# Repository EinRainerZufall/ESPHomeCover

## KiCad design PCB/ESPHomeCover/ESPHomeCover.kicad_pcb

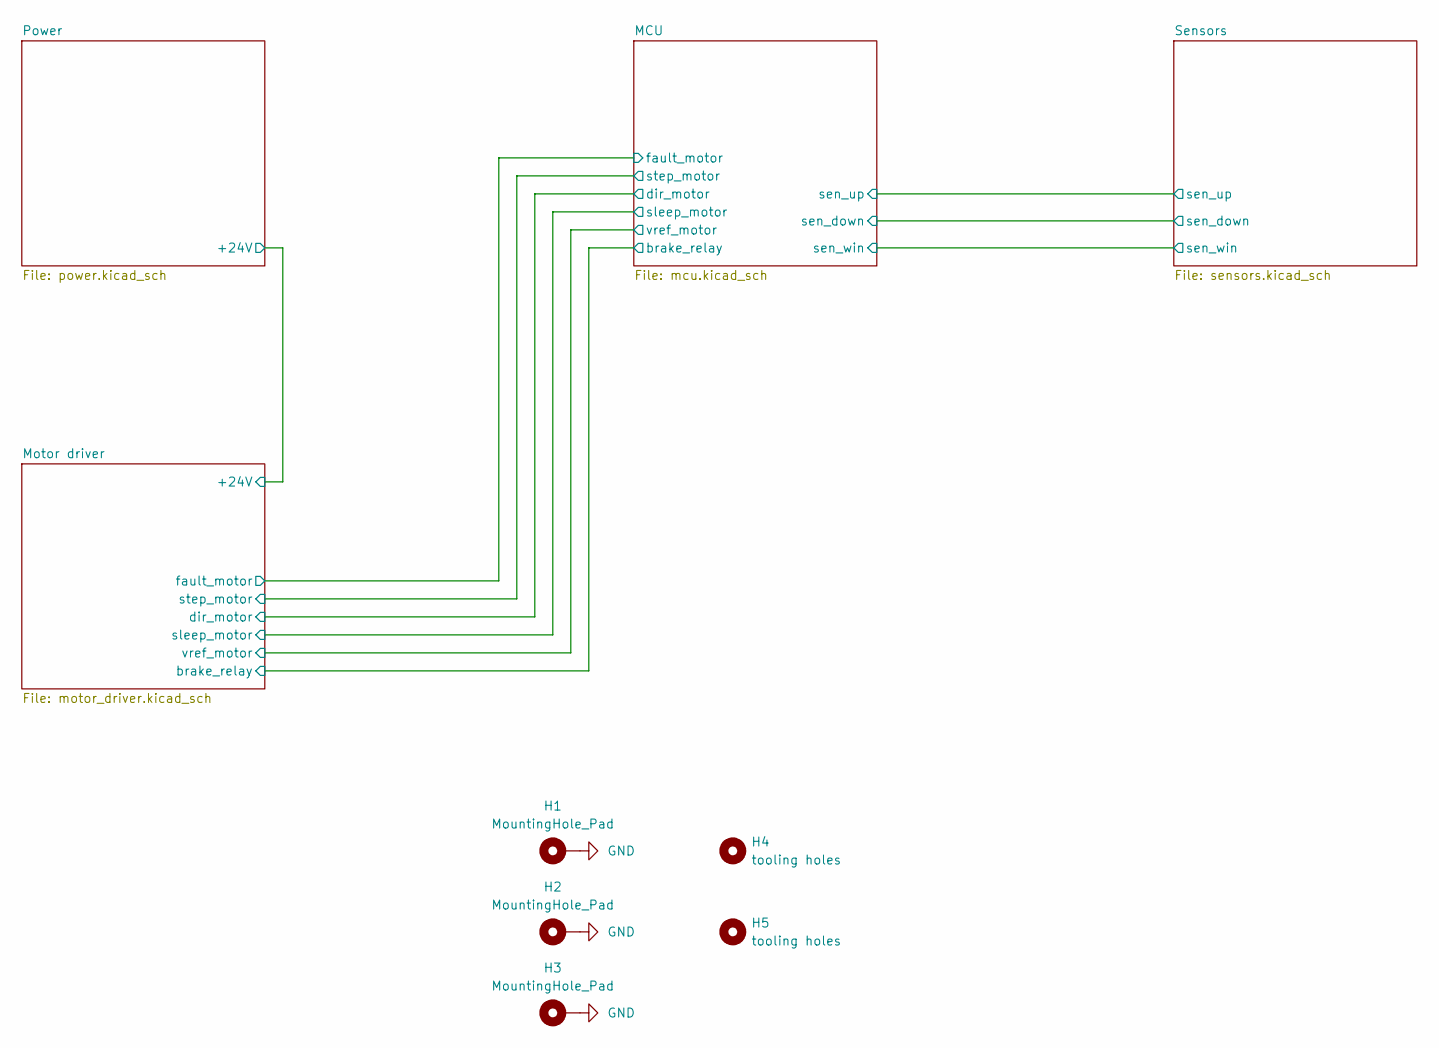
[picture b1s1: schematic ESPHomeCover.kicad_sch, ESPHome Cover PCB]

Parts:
H1, H2, H3: MountingHole_Pad; MountingHole_3.2mm_M3_ISO14580_Pad
H4, H5: tooling holes

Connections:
GND: H1.1, H2.1, H3.1; also elsewhere on the board

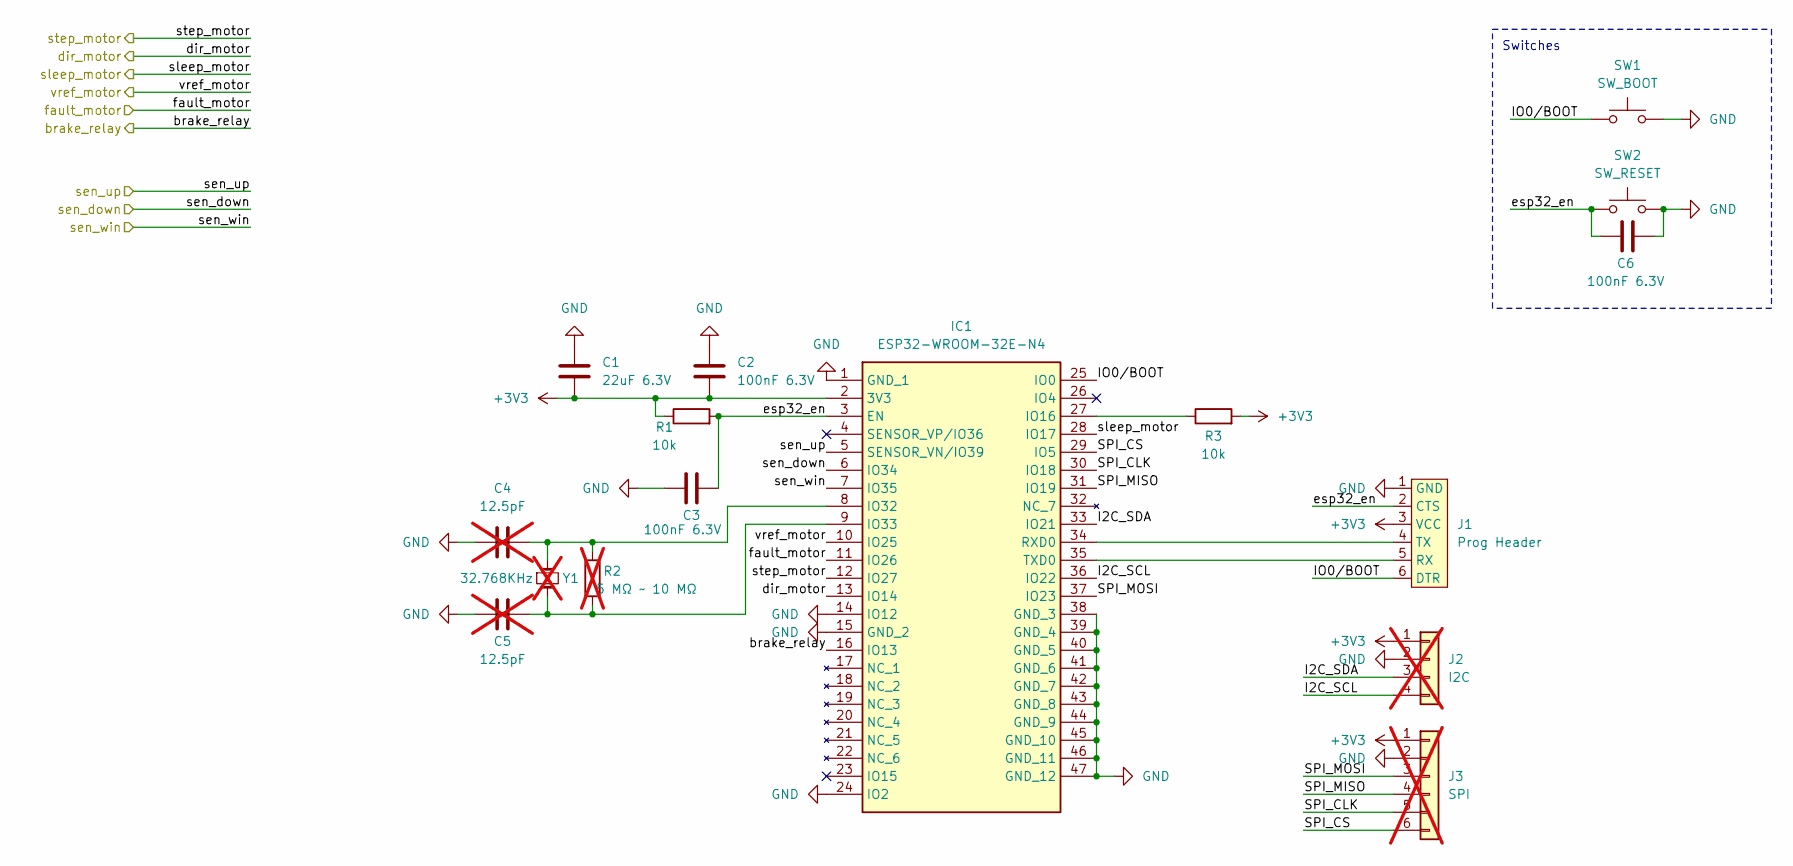
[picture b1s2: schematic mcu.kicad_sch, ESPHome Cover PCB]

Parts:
C1: 22uF 6.3V; C_0603_1608Metric; Mouser Part Number 963-MSASJ168BB5226MT; LCSC C159801
C2, C3, C6: 100nF 6.3V; C_0603_1608Metric; Mouser Part Number 581-06036C104JAT2A
C4, C5: 12.5pF; C_0603_1608Metric; not fitted
IC1: ESP32-WROOM-32E-N4; ESP32WROOM32EN4; Mouser Part Number 356-ESP32WRM32E132PH
J1: Prog Header
J2: I2C; JST_XH_B4B-XH-A_1x04_P2.50mm_Vertical; not fitted
J3: SPI; JST_XH_B6B-XH-A_1x06_P2.50mm_Vertical; not fitted
R1, R3: 10k; R_0805_2012Metric; Mouser Part Number 667-ERA-6AEB103V; LCSC C17414
R2: 5 MΩ ~ 10 MΩ; R_0805_2012Metric; not fitted
SW1: SW_BOOT; TL3302AF130QG; Mouser Part Number 612-TL3302AF130QG
SW2: SW_RESET; TL3302AF130QG; Mouser Part Number 612-TL3302AF130QG
Y1: 32.768KHz; Crystal_SMD_2012-2Pin_2.0x1.2mm; LCSC C5366544; not fitted

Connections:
+3V3: C1.2, C2.2, IC1.2 (3V3), J1.3 (VCC), J2.1, J3.1, R1.1, R3.2; also elsewhere on the board
/MCU/I2C_SCL: IC1.36 (IO22), J2.4
/MCU/I2C_SDA: IC1.33 (IO21), J2.3
/MCU/IO0/BOOT: IC1.25 (IO0), J1.6 (DTR), SW1.1
/MCU/SPI_CLK: IC1.30 (IO18), J3.5
/MCU/SPI_CS: IC1.29 (IO5), J3.6
/MCU/SPI_MISO: IC1.31 (IO19), J3.4
/MCU/SPI_MOSI: IC1.37 (IO23), J3.3
/MCU/brake_relay: IC1.16 (IO13); also elsewhere on the board
/MCU/dir_motor: IC1.13 (IO14); also elsewhere on the board
/MCU/esp32_en: C3.2, C6.2, IC1.3 (EN), J1.2 (CTS), R1.2, SW2.2
/MCU/fault_motor: IC1.11 (IO26); also elsewhere on the board
/MCU/sen_down: IC1.6 (IO34); also elsewhere on the board
/MCU/sen_up: IC1.5 (SENSOR_VN/IO39); also elsewhere on the board
/MCU/sen_win: IC1.7 (IO35); also elsewhere on the board
/MCU/sleep_motor: IC1.28 (IO17); also elsewhere on the board
/MCU/step_motor: IC1.12 (IO27); also elsewhere on the board
/MCU/vref_motor: IC1.10 (IO25); also elsewhere on the board
GND: C1.1, C2.1, C3.1, C4.1, C5.1, C6.1, IC1.1 (GND_1), IC1.14 (IO12), IC1.15 (GND_2), IC1.24 (IO2), IC1.38 (GND_3), IC1.39 (GND_4), IC1.40 (GND_5), IC1.41 (GND_6), IC1.42 (GND_7), IC1.43 (GND_8), IC1.44 (GND_9), IC1.45 (GND_10), IC1.46 (GND_11), IC1.47 (GND_12), J1.1 (GND), J2.2, J3.2, SW1.2, SW2.1; also elsewhere on the board
unnamed: IC1.27 (IO16), R3.1
unnamed: C4.2, IC1.8 (IO32), R2.2, Y1.1
unnamed: C5.2, IC1.9 (IO33), R2.1, Y1.2
unnamed: IC1.34 (RXD0), J1.4 (TX)
unnamed: IC1.35 (TXD0), J1.5 (RX)

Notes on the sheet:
Switches

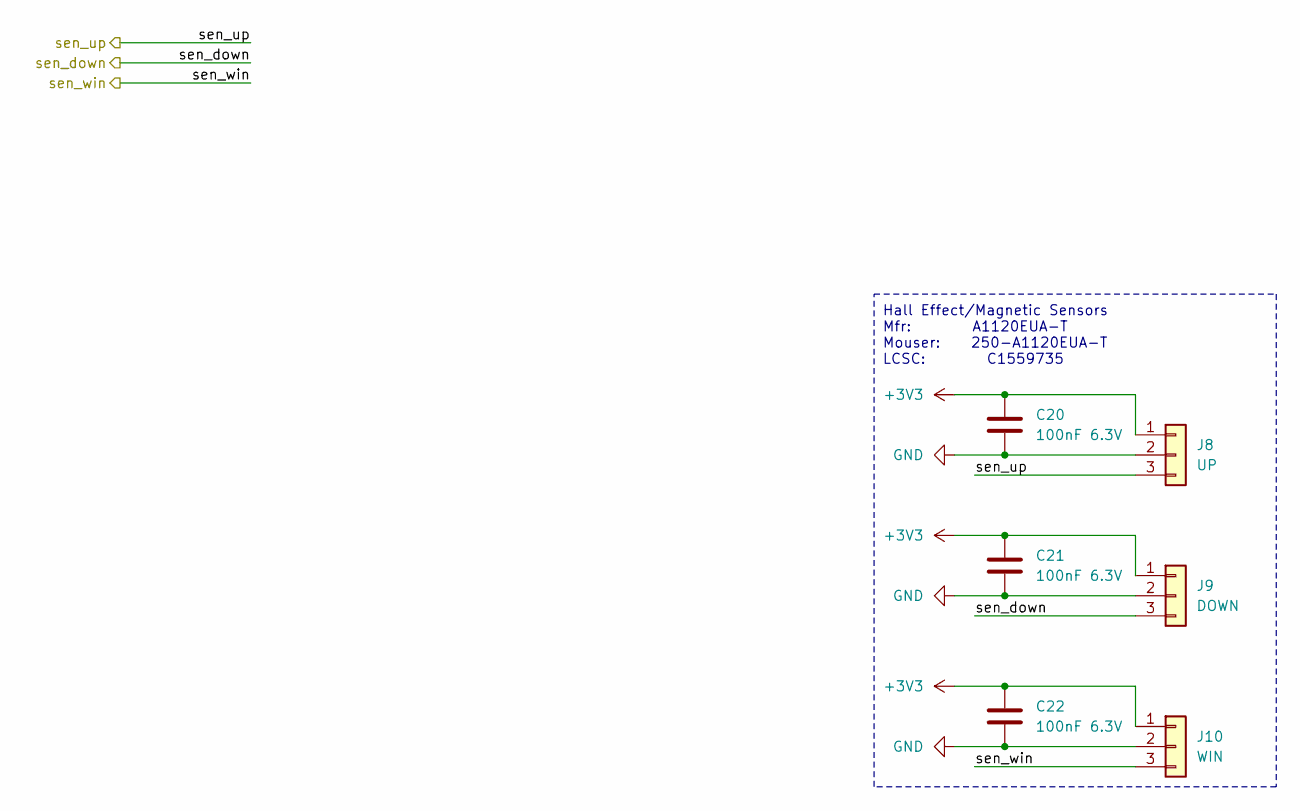
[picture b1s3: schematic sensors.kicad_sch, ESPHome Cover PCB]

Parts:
C20, C21, C22: 100nF 6.3V; C_0603_1608Metric; Mouser Part Number 581-06036C104JAT2A
J8: UP; JST_XH_B3B-XH-A_1x03_P2.50mm_Vertical
J9: DOWN; JST_XH_B3B-XH-A_1x03_P2.50mm_Vertical
J10: WIN; JST_XH_B3B-XH-A_1x03_P2.50mm_Vertical

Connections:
+3V3: C20.1, C21.1, C22.1, J8.1, J9.1, J10.1; also elsewhere on the board
/MCU/sen_down: J9.3; also elsewhere on the board
/MCU/sen_up: J8.3; also elsewhere on the board
/MCU/sen_win: J10.3; also elsewhere on the board
GND: C20.2, C21.2, C22.2, J8.2, J9.2, J10.2; also elsewhere on the board

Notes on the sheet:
Hall Effect/Magnetic Sensors Mfr: A1120EUA-T Mouser: 250-A1120EUA-T LCSC: C1559735

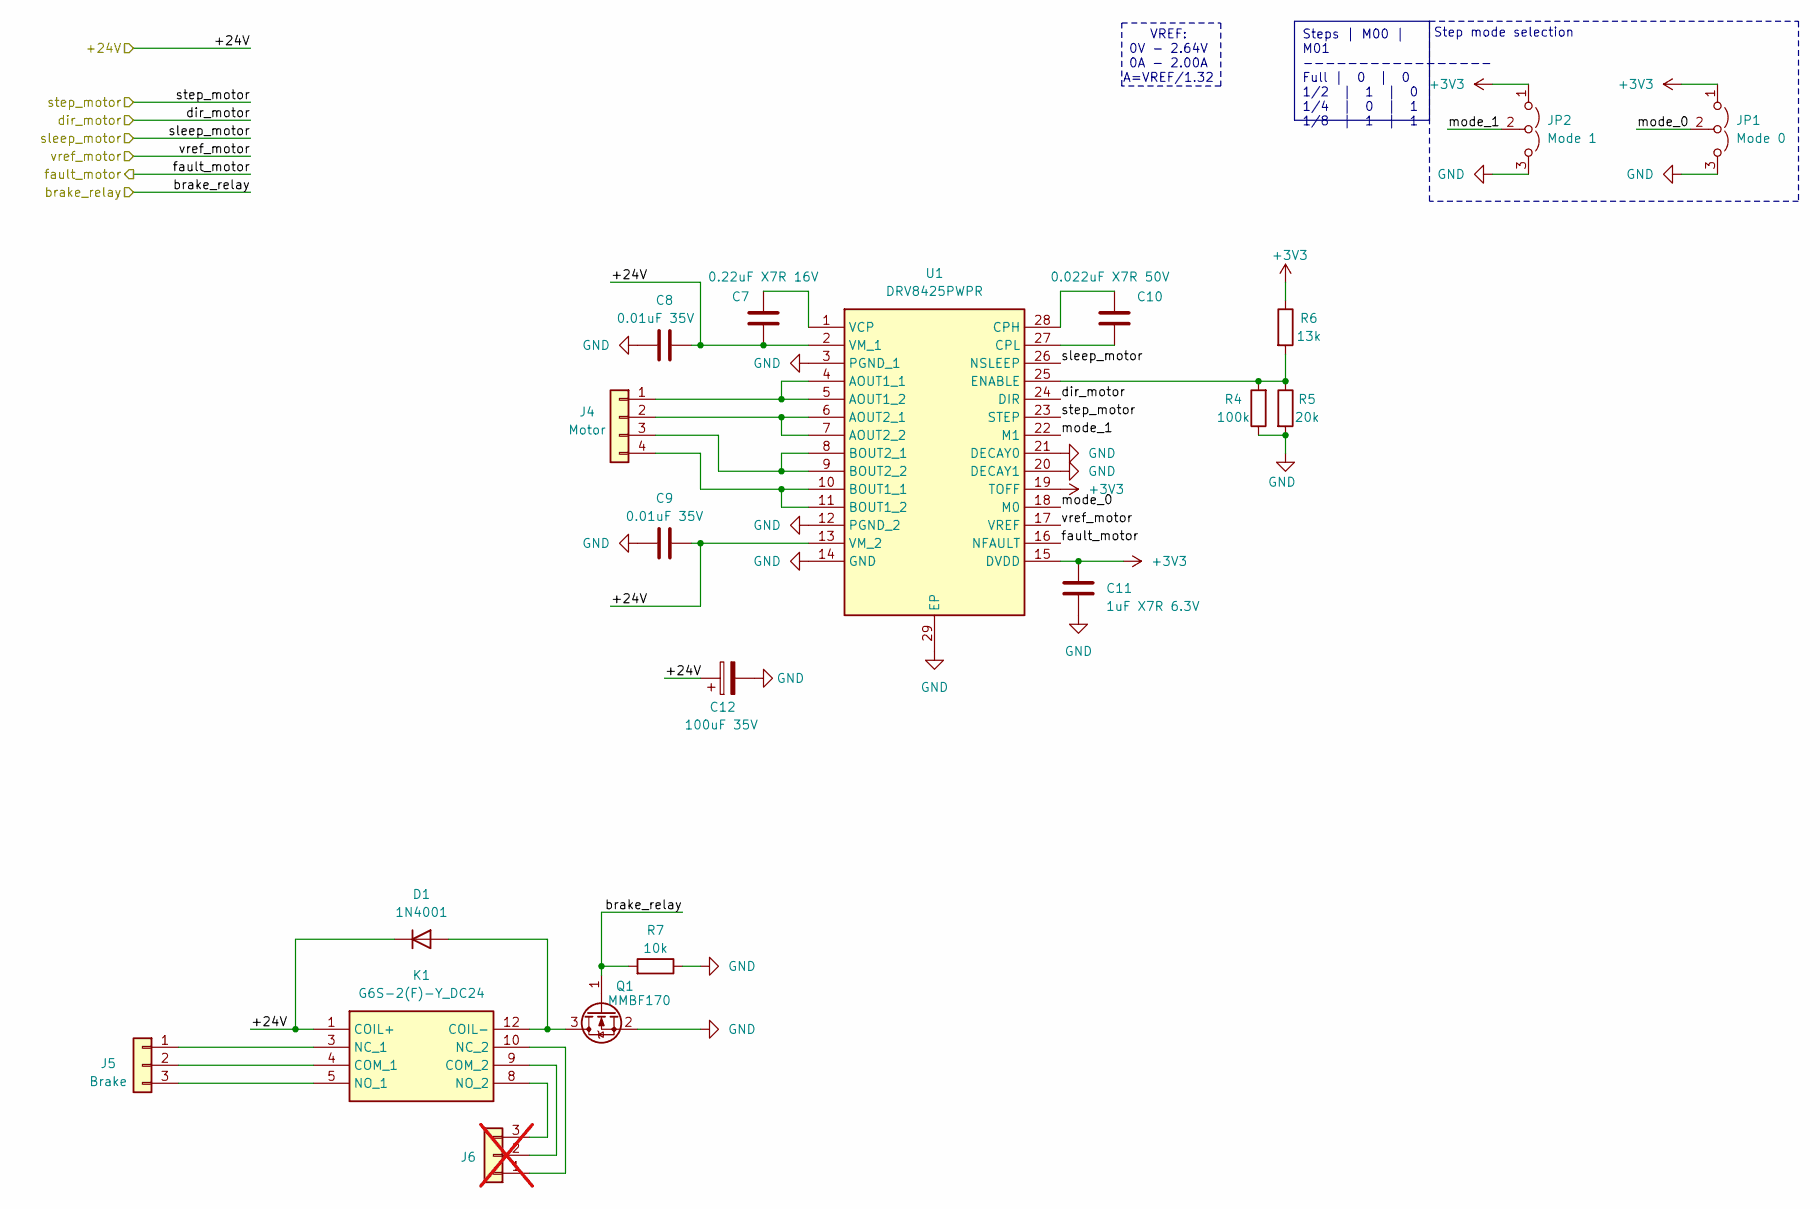
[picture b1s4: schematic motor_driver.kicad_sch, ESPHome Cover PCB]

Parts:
C7: 0.22uF X7R 16V; C_0603_1608Metric; Mouser Part Number 80-C0603C224K4R
C8, C9: 0.01uF 35V; C_0603_1608Metric; Mouser Part Number 810-C1608C0G1V153JAC
C10: 0.022uF X7R 50V; C_0603_1608Metric; Mouser Part Number 581-06035C223KAT4A; LCSC C77571
C11: 1uF X7R 6.3V; C_0603_1608Metric; Mouser Part Number 581-06035C105KAT2A; LCSC C309479
C12: 100uF 35V; CP_Elec_6.3x7.7; Mouser Part Number 667-EEH-ZK1V101XP; LCSC C72478
D1: 1N4001; D_DO-41_SOD81_P10.16mm_Horizontal; Mouser Part Number 637-1N4001; LCSC C727079
J4: Motor; JST_XH_B4B-XH-A_1x04_P2.50mm_Vertical
J5: Brake; JST_XH_B3B-XH-A_1x03_P2.50mm_Vertical
J6: PinHeader_1x03_P2.54mm_Vertical; not fitted
JP1: Mode 0; PinHeader_1x03_P2.54mm_Vertical_SMD_Pin1Left; LCSC C780061
JP2: Mode 1; PinHeader_1x03_P2.54mm_Vertical_SMD_Pin1Left; LCSC C780061
K1: G6S-2(F)-Y_DC24; G6S2(F)YDC24; Mouser Part Number 653-G6S-2F-YDC241
Q1: MMBF170; SOT-23; Mouser Part Number 512-MMBF170; LCSC C151058
R4: 100k; R_0805_2012Metric; Mouser Part Number 71-CRCW0805100KJNECC; LCSC C149504
R5: 20k; R_0805_2012Metric; Mouser Part Number 71-CRCW080520K0FKEAH; LCSC C4328
R6: 13k; R_0805_2012Metric; Mouser Part Number 71-CRCW080513K0JNEA; LCSC C17455
R7: 10k; R_0805_2012Metric; Mouser Part Number 667-ERA-6AEB103V; LCSC C17414
U1: DRV8425PWPR; SOP65P640X120-29N; Mouser Part Number 595-DRV8425PWPR

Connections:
+3V3: C11.1, JP1.1 (A), JP2.1 (A), R6.1, U1.15 (DVDD), U1.19 (TOFF); also elsewhere on the board
/MCU/brake_relay: Q1.1 (G), R7.2; also elsewhere on the board
/MCU/dir_motor: U1.24 (DIR); also elsewhere on the board
/MCU/fault_motor: U1.16 (NFAULT); also elsewhere on the board
/MCU/sleep_motor: U1.26 (NSLEEP); also elsewhere on the board
/MCU/step_motor: U1.23 (STEP); also elsewhere on the board
/MCU/vref_motor: U1.17 (VREF); also elsewhere on the board
/Motor driver/+24V: C7.2, C8.2, C9.2, C12.1, D1.1 (K), K1.1 (COIL+), U1.2 (VM_1), U1.13 (VM_2); also elsewhere on the board
/Motor driver/mode_0: JP1.2 (C), U1.18 (M0)
/Motor driver/mode_1: JP2.2 (C), U1.22 (M1)
GND: C8.1, C9.1, C11.2, C12.2, JP1.3 (B), JP2.3 (B), Q1.2 (S), R4.1, R5.2, R7.1, U1.3 (PGND_1), U1.12 (PGND_2), U1.14 (GND), U1.20 (DECAY1), U1.21 (DECAY0), U1.29 (EP); also elsewhere on the board
unnamed: D1.2 (A), K1.12 (COIL-), Q1.3 (D)
unnamed: J4.1, U1.4 (AOUT1_1), U1.5 (AOUT1_2)
unnamed: J4.2, U1.6 (AOUT2_1), U1.7 (AOUT2_2)
unnamed: J4.3, U1.8 (BOUT2_1), U1.9 (BOUT2_2)
unnamed: J4.4, U1.10 (BOUT1_1), U1.11 (BOUT1_2)
unnamed: J5.1, K1.3 (NC_1)
unnamed: J5.2, K1.4 (COM_1)
unnamed: J5.3, K1.5 (NO_1)
unnamed: J6.1, K1.10 (NC_2)
unnamed: J6.2, K1.9 (COM_2)
unnamed: J6.3, K1.8 (NO_2)
unnamed: C10.1, U1.28 (CPH)
unnamed: C10.2, U1.27 (CPL)
unnamed: R4.2, R5.1, R6.2, U1.25 (ENABLE)
unnamed: C7.1, U1.1 (VCP)

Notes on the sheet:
Steps | M00 | M01 ----------------- Full | 0 | 0 1/2 | 1 | 0 1/4 | 0 | 1 1/8 | 1 | 1
VREF: 0V - 2.64V 0A - 2.00A A=VREF/1.32
Step mode selection

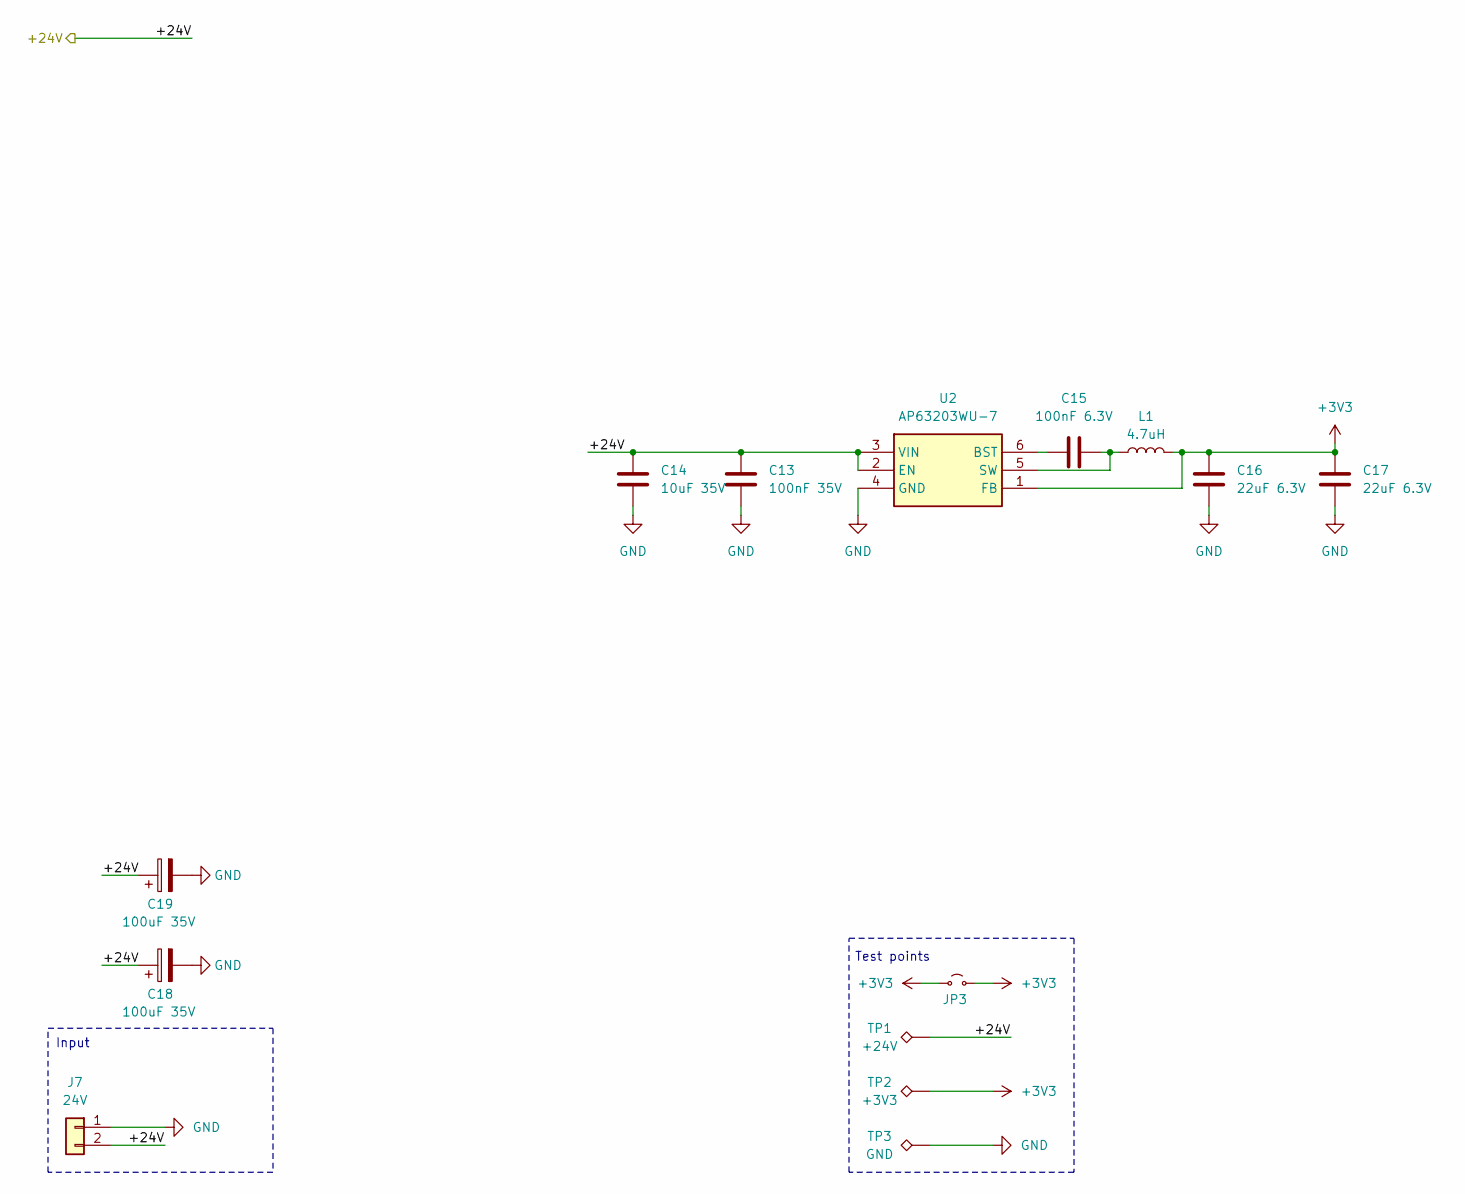
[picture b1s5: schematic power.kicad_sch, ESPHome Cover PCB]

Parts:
C13: 100nF 35V; C_0603_1608Metric; Mouser Part Number 963-GMK107B7104KAHT; LCSC C385964
C14: 10uF 35V; C_0603_1608Metric; Mouser Part Number 81-GRM188R6YA106MA3J; LCSC C194427
C15: 100nF 6.3V; C_0603_1608Metric; Mouser Part Number 581-06036C104JAT2A
C16, C17: 22uF 6.3V; C_0603_1608Metric; Mouser Part Number 963-MSASJ168BB5226MT; LCSC C159801
C18, C19: 100uF 35V; CP_Elec_6.3x7.7; Mouser Part Number 667-EEH-ZK1V101XP; LCSC C72478
J7: 24V; JST_XH_B2B-XH-A_1x02_P2.50mm_Vertical
JP3: SolderJumper-2_P1.3mm_Open_RoundedPad1.0x1.5mm
L1: 4.7uH; L_1812_4532Metric; Mouser Part Number 871-B82432T1472K; LCSC C394118
TP1: +24V; TestPoint_Pad_1.0x1.0mm
TP2: +3V3; TestPoint_Pad_1.0x1.0mm
TP3: GND; TestPoint_Pad_1.0x1.0mm
U2: AP63203WU-7; TSOT-23-6; Mouser Part Number 621-AP63203WU-7

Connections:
+3V3: C16.1, C17.1, JP3.1 (A), JP3.2 (B), L1.2, TP2.1, U2.1 (FB); also elsewhere on the board
/Motor driver/+24V: C13.1, C14.1, C18.1, C19.1, J7.2, TP1.1, U2.2 (EN), U2.3 (VIN); also elsewhere on the board
GND: C13.2, C14.2, C16.2, C17.2, C18.2, C19.2, J7.1, TP3.1, U2.4 (GND); also elsewhere on the board
unnamed: C15.1, U2.6 (BST)
unnamed: C15.2, L1.1, U2.5 (SW)

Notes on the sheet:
Input
Test points

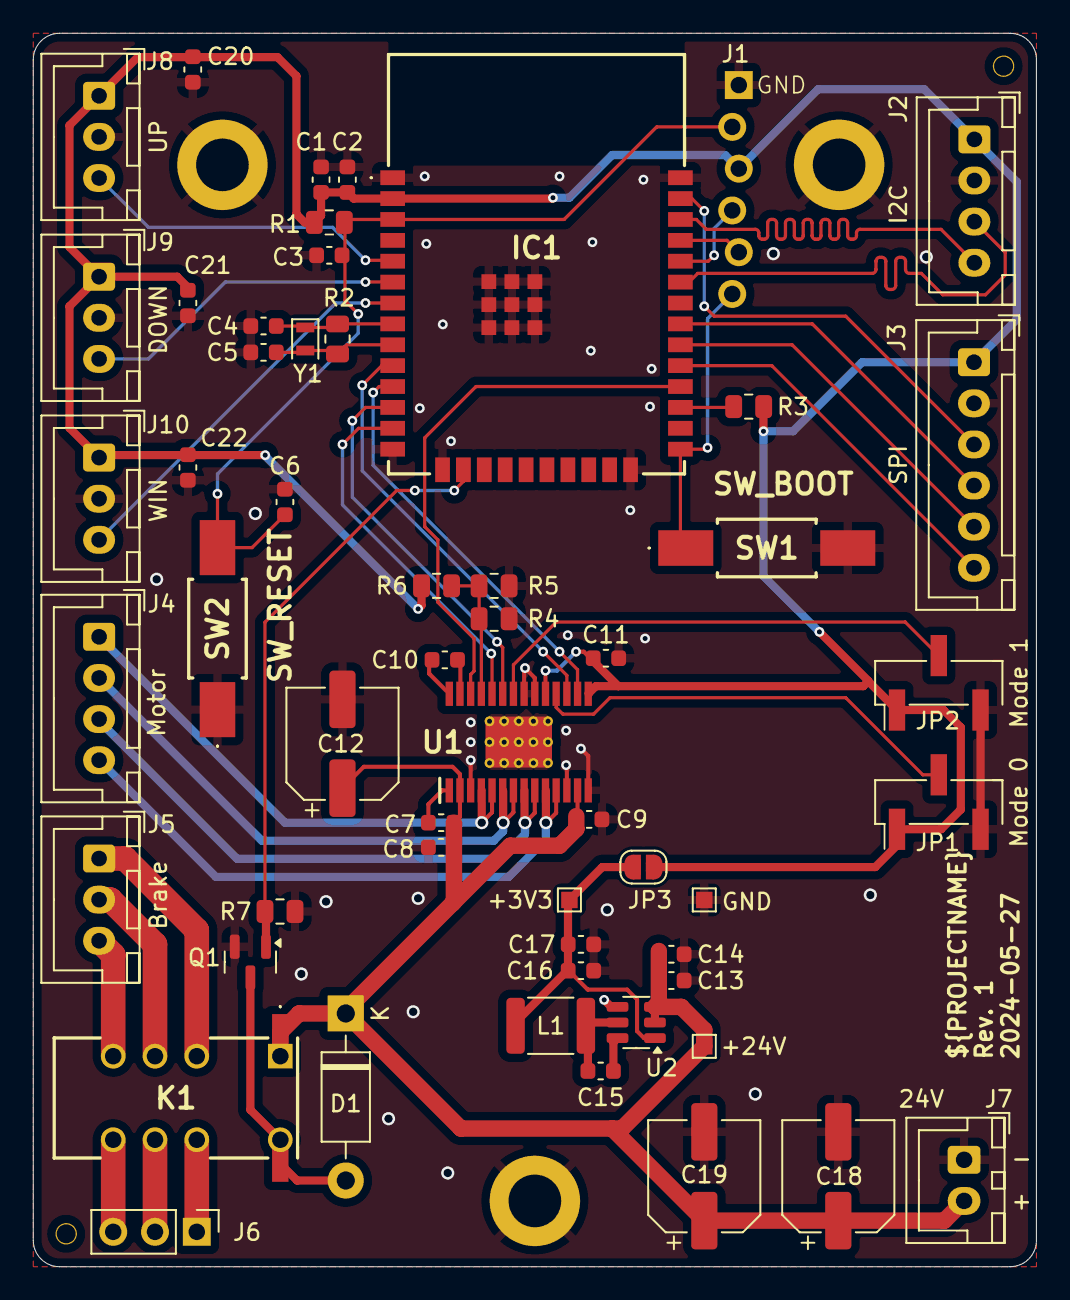
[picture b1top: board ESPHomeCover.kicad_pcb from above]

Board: 2 copper layers, 61.0 x 75.0 mm, 60 parts (0 on the bottom side), 44 nets.

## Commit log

2024-03-02 add purchase parts
2024-03-05 update motor holder
2024-05-02 rework of the old models
2024-05-02 improved printability
2024-05-08 create V1 schematic
2024-05-08 Add Board
2024-05-12 small changes
    change all Caps to 0603,
    add bom
2024-05-26 update PCB
